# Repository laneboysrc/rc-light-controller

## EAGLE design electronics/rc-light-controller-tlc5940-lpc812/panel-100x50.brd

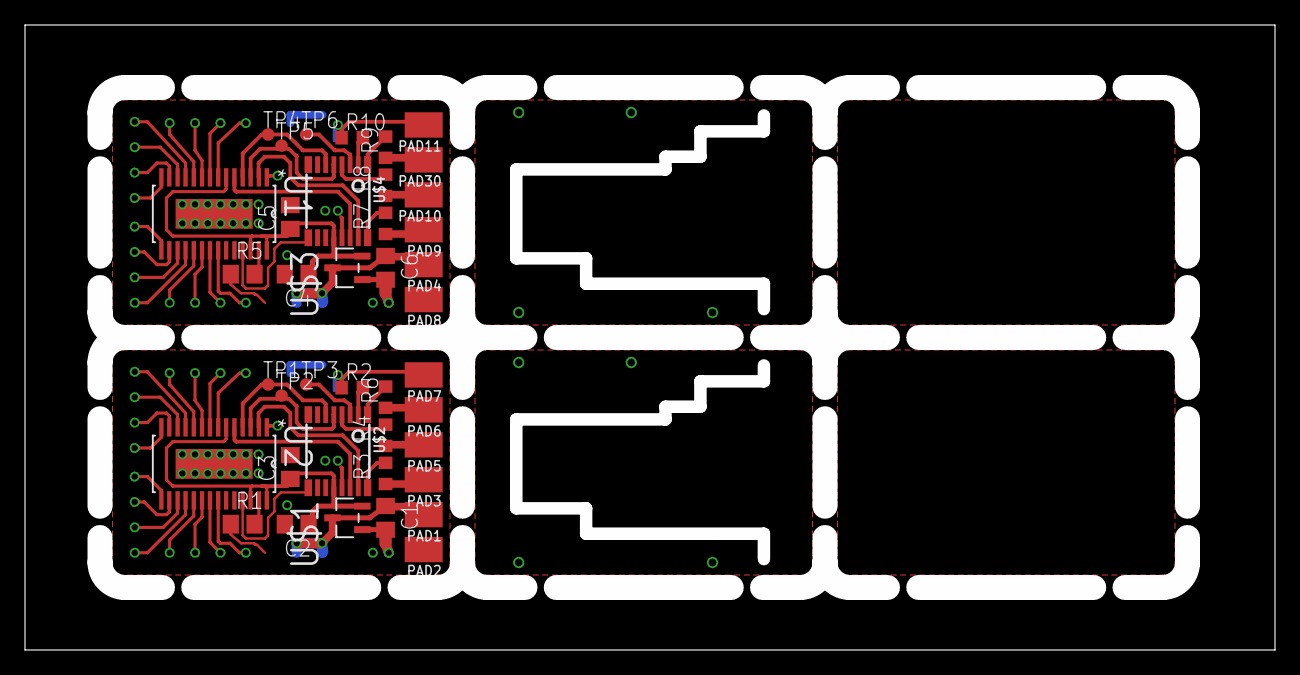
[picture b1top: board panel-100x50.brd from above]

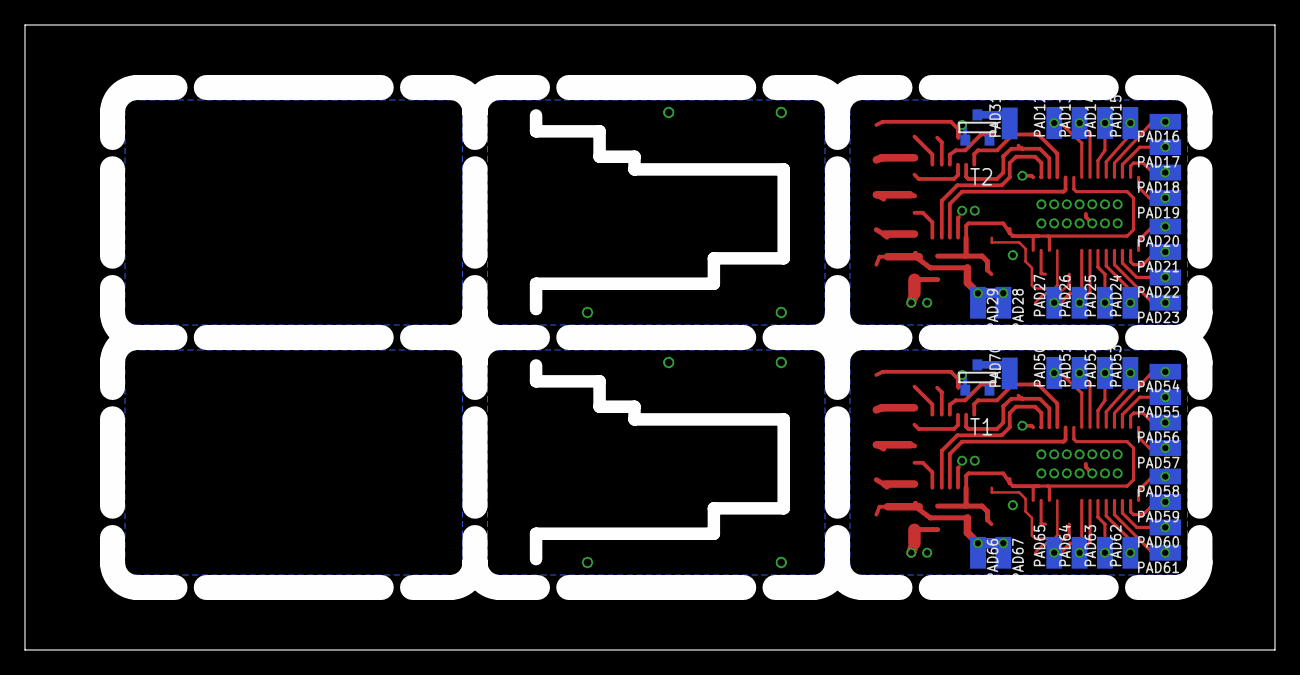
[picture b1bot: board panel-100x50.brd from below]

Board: 2 copper layers, 100.0 x 50.0 mm, 80 parts (40 on the bottom side), 70 nets.

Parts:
C1, C2, C4, C6: 1u; C0805
C3, C5: 100n; C0805
PAD1, PAD4: +; SMD80X120
PAD2, PAD8: -; SMD80X120
PAD3, PAD9: ST/Rx; SMD80X120
PAD5, PAD10: TH/Tx; SMD80X120
PAD6, PAD30: CH3; SMD80X120
PAD7, PAD11: OUT/ISP; SMD80X120
PAD12, PAD13, PAD14, PAD15, PAD16, PAD17, PAD18, PAD19, PAD20, PAD21, PAD22, PAD23, PAD24, PAD25, PAD26, PAD27, PAD28, PAD29, PAD31, PAD50, PAD51, PAD52, PAD53, PAD54, PAD55, PAD56, PAD57, PAD58, PAD59, PAD60, PAD61, PAD62, PAD63, PAD64, PAD65, PAD66, PAD67, PAD70: SMD50X100
R1, R5: 2k0=20mA; R0805
R2, R3, R4, R6, R7, R8, R9, R10: 1k; R0603
T1, T2: SOT-23
TP1, TP4: SWDIO; TP10R
TP2, TP5: SWCLK; TP10R
TP3, TP6: RESET; TP10R
U1, U2: TLC5940PWP; SOP65P640X120-29N
U$1, U$3: 3V3; SOT95P300X145-3N
U$2, U$4: LPC812; TSSOP16

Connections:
+3V1: C4.1, C5.1, U1.6, U1.26, U1.28, U$3.2, U$4.12
+3V3: C2.1, C3.1, U2.6, U2.26, U2.28, U$1.2, U$2.12
BLANK: U2.2, U$2.15
BLANK1: U1.2, U$4.15
CH1: R9.2, U$4.1
CH3: R6.2, U$2.1
GND: C1.2, C2.2, C3.2, PAD2.1, R1.1, T1.2, U2.1, U2.29, U$1.1, U$2.13
GND1: C4.2, C5.2, C6.2, PAD8.1, R5.1, T2.2, U1.1, U1.29, U$3.1, U$4.13
GSCLK: U2.25, U$2.9
GSCLK1: U1.25, U$4.9
IREF: R1.2, U2.27
IREF1: R5.2, U1.27
unnamed: PAD6.1, R6.1
unnamed: PAD7.1, R2.1, T1.3
unnamed: PAD70.1, T1.1
unnamed: TP3.TP, U$2.3
unnamed: PAD9.1, R7.1
unnamed: PAD10.1, R8.1
unnamed: PAD30.1, R9.1
unnamed: TP6.TP, U$4.3
unnamed: PAD31.1, T2.1
unnamed: PAD11.1, R10.1, T2.3
unnamed: PAD3.1, R3.1
unnamed: PAD5.1, R4.1
OUT0: PAD50.1, U2.7
OUT1: PAD51.1, U2.8
OUT2: PAD52.1, U2.9
OUT3: PAD53.1, U2.10
OUT4: PAD54.1, U2.11
OUT5: PAD55.1, U2.12
OUT6: PAD56.1, U2.13
OUT7: PAD57.1, U2.14
OUT8: PAD58.1, U2.15
OUT9: PAD59.1, U2.16
OUT10: PAD60.1, U2.17
OUT11: PAD61.1, U2.18
OUT12: PAD62.1, U2.19
OUT13: PAD63.1, U2.20
OUT14: PAD64.1, U2.21
OUT15: PAD65.1, U2.22
OUT16: PAD12.1, U1.7
OUT17: PAD13.1, U1.8
OUT18: PAD14.1, U1.9
OUT19: PAD15.1, U1.10
OUT20: PAD27.1, U1.22
OUT21: PAD26.1, U1.21
OUT22: PAD25.1, U1.20
OUT23: PAD24.1, U1.19
OUT24: PAD23.1, U1.18
OUT25: PAD22.1, U1.17
OUT26: PAD21.1, U1.16
OUT27: PAD20.1, U1.15
OUT28: PAD19.1, U1.14
OUT29: PAD18.1, U1.13
OUT30: PAD17.1, U1.12
OUT31: PAD16.1, U1.11
OUT/ISP: R2.2, U$2.2
OUT/ISP1: R10.2, U$4.2
SCLK: TP1.TP, U2.4, U$2.6
SCLK1: TP4.TP, U1.4, U$4.6
SIN: U2.5, U$2.14
SIN1: U1.5, U$4.14
ST/RX: R3.2, U$2.16
ST/RX1: R7.2, U$4.16
TH/TX: R4.2, U$2.4
TH/TX1: R8.2, U$4.4
VIN: C1.1, PAD1.1, PAD66.1, PAD67.1, U$1.3
VIN1: C6.1, PAD4.1, PAD28.1, PAD29.1, U$3.3
XLAT: TP2.TP, U2.3, U$2.5
XLAT1: TP5.TP, U1.3, U$4.5

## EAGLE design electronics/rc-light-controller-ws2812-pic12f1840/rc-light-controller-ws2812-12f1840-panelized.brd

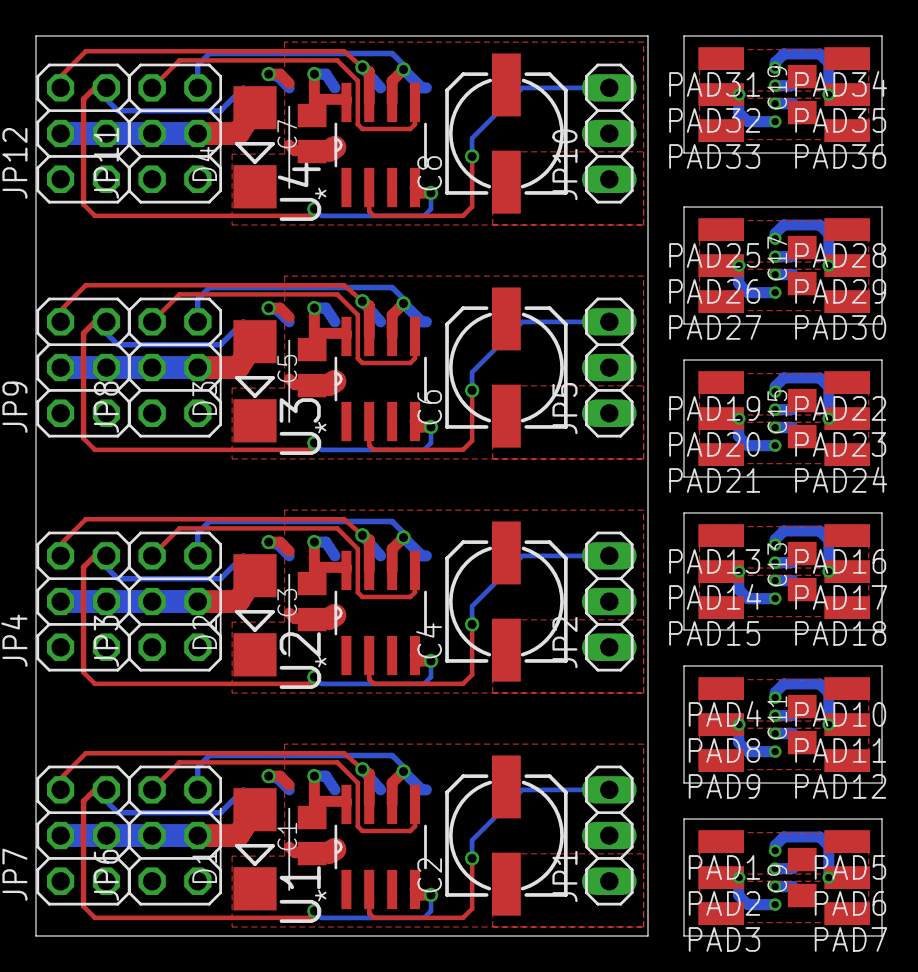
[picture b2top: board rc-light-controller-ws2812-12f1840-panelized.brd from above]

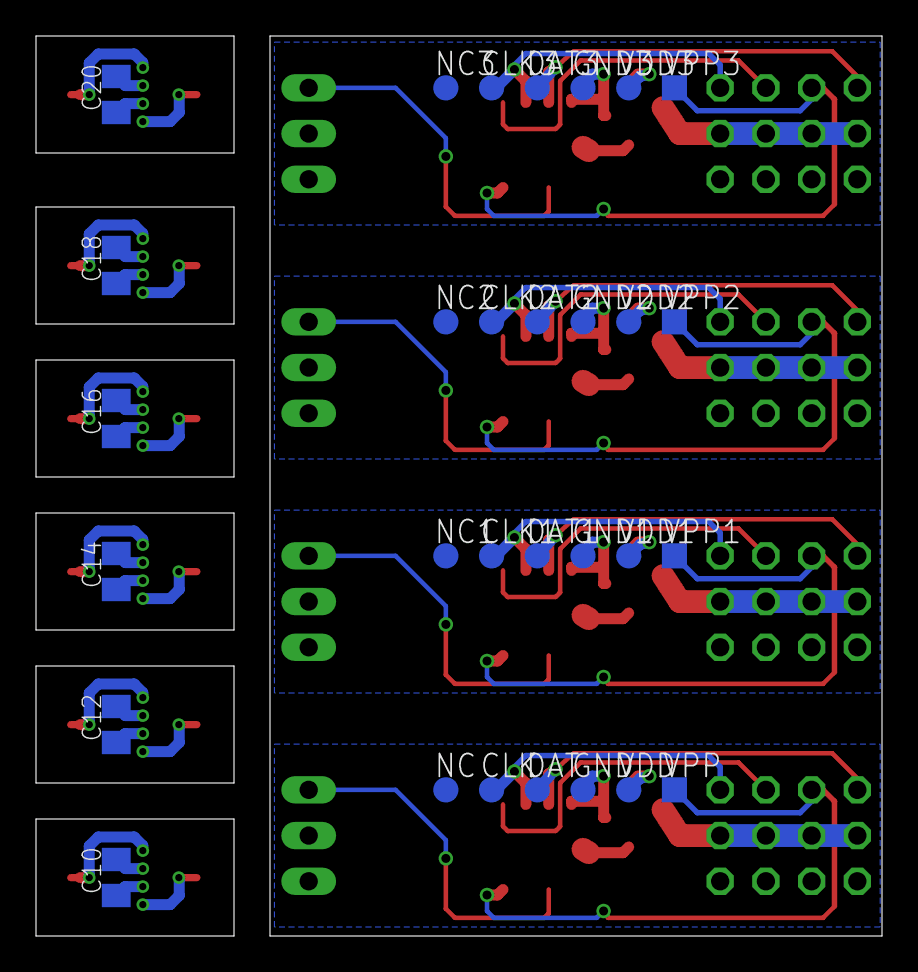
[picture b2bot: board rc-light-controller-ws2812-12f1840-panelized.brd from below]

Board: 2 copper layers, 47.0 x 50.0 mm, 100 parts (30 on the bottom side), 44 nets.

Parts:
C1, C3, C5, C7: 100n; C0805K
C2, C4, C6, C8: 100u 16V; 153CLV-0605
C9, C10, C11, C12, C13, C14, C15, C16, C17, C18, C19, C20: 100nF; C0805K
CLK, CLK1, CLK2, CLK3: PTR1TP14R; TP14R
D1, D2, D3, D4: ES2D; SMB
DAT, DAT1, DAT2, DAT3: PTR1TP14R; TP14R
GND, GND1, GND2, GND3: PTR1TP14R; TP14R
JP1, JP2, JP5, JP10: LED OUT; 1X03
JP3, JP4, JP6, JP7, JP8, JP9, JP11, JP12: 2X03
NC, NC1, NC2, NC3: PTR1TP14R; TP14R
PAD1, PAD4, PAD13, PAD19, PAD25, PAD31: SMD1,27-2,54
PAD2, PAD3, PAD5, PAD6, PAD7, PAD8, PAD9, PAD10, PAD11, PAD12, PAD14, PAD15, PAD16, PAD17, PAD18, PAD20, PAD21, PAD22, PAD23, PAD24, PAD26, PAD27, PAD28, PAD29, PAD30, PAD32, PAD33, PAD34, PAD35, PAD36: WIREPADSMD1,27-254; SMD1,27-2,54
U1, U2, U3, U4: 12F1840; SOIC127P600X175-8N
VDD, VDD1, VDD2, VDD3: PTR1TP14R; TP14R
VPP, VPP1, VPP2, VPP3: PTR1TP14SQ; TP14SQ

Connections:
+: C9.1, C10.1, PAD3.1, PAD7.1
+1: C11.1, C12.1, PAD9.1, PAD12.1
+2: C13.1, C14.1, PAD15.1, PAD18.1
+3: C15.1, C16.1, PAD21.1, PAD24.1
+4: C17.1, C18.1, PAD27.1, PAD30.1
+5: C19.1, C20.1, PAD33.1, PAD36.1
-: C9.2, C10.2, PAD1.1, PAD5.1
-1: C11.2, C12.2, PAD4.1, PAD10.1
-2: C13.2, C14.2, PAD13.1, PAD16.1
-3: C15.2, C16.2, PAD19.1, PAD22.1
-4: C17.2, C18.2, PAD25.1, PAD28.1
-5: C19.2, C20.2, PAD31.1, PAD34.1
CH1: JP4.5, U2.4, VPP1.TP
CH2: JP9.5, U3.4, VPP2.TP
CH3: JP7.5, U1.4, VPP.TP
CH4: JP12.5, U4.4, VPP3.TP
GND: C1.2, C2.-, GND.TP, JP1.1, JP6.1, JP6.2, JP7.1, JP7.2, U1.8
GND1: C3.2, C4.-, GND1.TP, JP2.1, JP3.1, JP3.2, JP4.1, JP4.2, U2.8
GND2: C5.2, C6.-, GND2.TP, JP5.1, JP8.1, JP8.2, JP9.1, JP9.2, U3.8
GND3: C7.2, C8.-, GND3.TP, JP10.1, JP11.1, JP11.2, JP12.1, JP12.2, U4.8
unnamed: JP2.3, U2.2
unnamed: JP5.3, U3.2
unnamed: JP10.3, U4.2
unnamed: JP1.3, U1.2
OUT/TX: DAT.TP, JP7.6, U1.7
OUT/TX1: DAT1.TP, JP4.6, U2.7
OUT/TX2: DAT2.TP, JP9.6, U3.7
OUT/TX3: DAT3.TP, JP12.6, U4.7
ST/RX: CLK.TP, JP6.5, U1.6
ST/RX1: CLK1.TP, JP3.5, U2.6
ST/RX2: CLK2.TP, JP8.5, U3.6
ST/RX3: CLK3.TP, JP11.5, U4.6
TH: JP6.6, U1.5
TH1: JP3.6, U2.5
TH2: JP8.6, U3.5
TH3: JP11.6, U4.5
VBAT: D1.A, JP6.3, JP6.4, JP7.3, JP7.4
VBAT1: D2.A, JP3.3, JP3.4, JP4.3, JP4.4
VBAT2: D3.A, JP8.3, JP8.4, JP9.3, JP9.4
VBAT3: D4.A, JP11.3, JP11.4, JP12.3, JP12.4
VDD: C1.1, C2.+, D1.C, JP1.2, U1.1, VDD.TP
VDD1: C3.1, C4.+, D2.C, JP2.2, U2.1, VDD1.TP
VDD2: C5.1, C6.+, D3.C, JP5.2, U3.1, VDD2.TP
VDD3: C7.1, C8.+, D4.C, JP10.2, U4.1, VDD3.TP
